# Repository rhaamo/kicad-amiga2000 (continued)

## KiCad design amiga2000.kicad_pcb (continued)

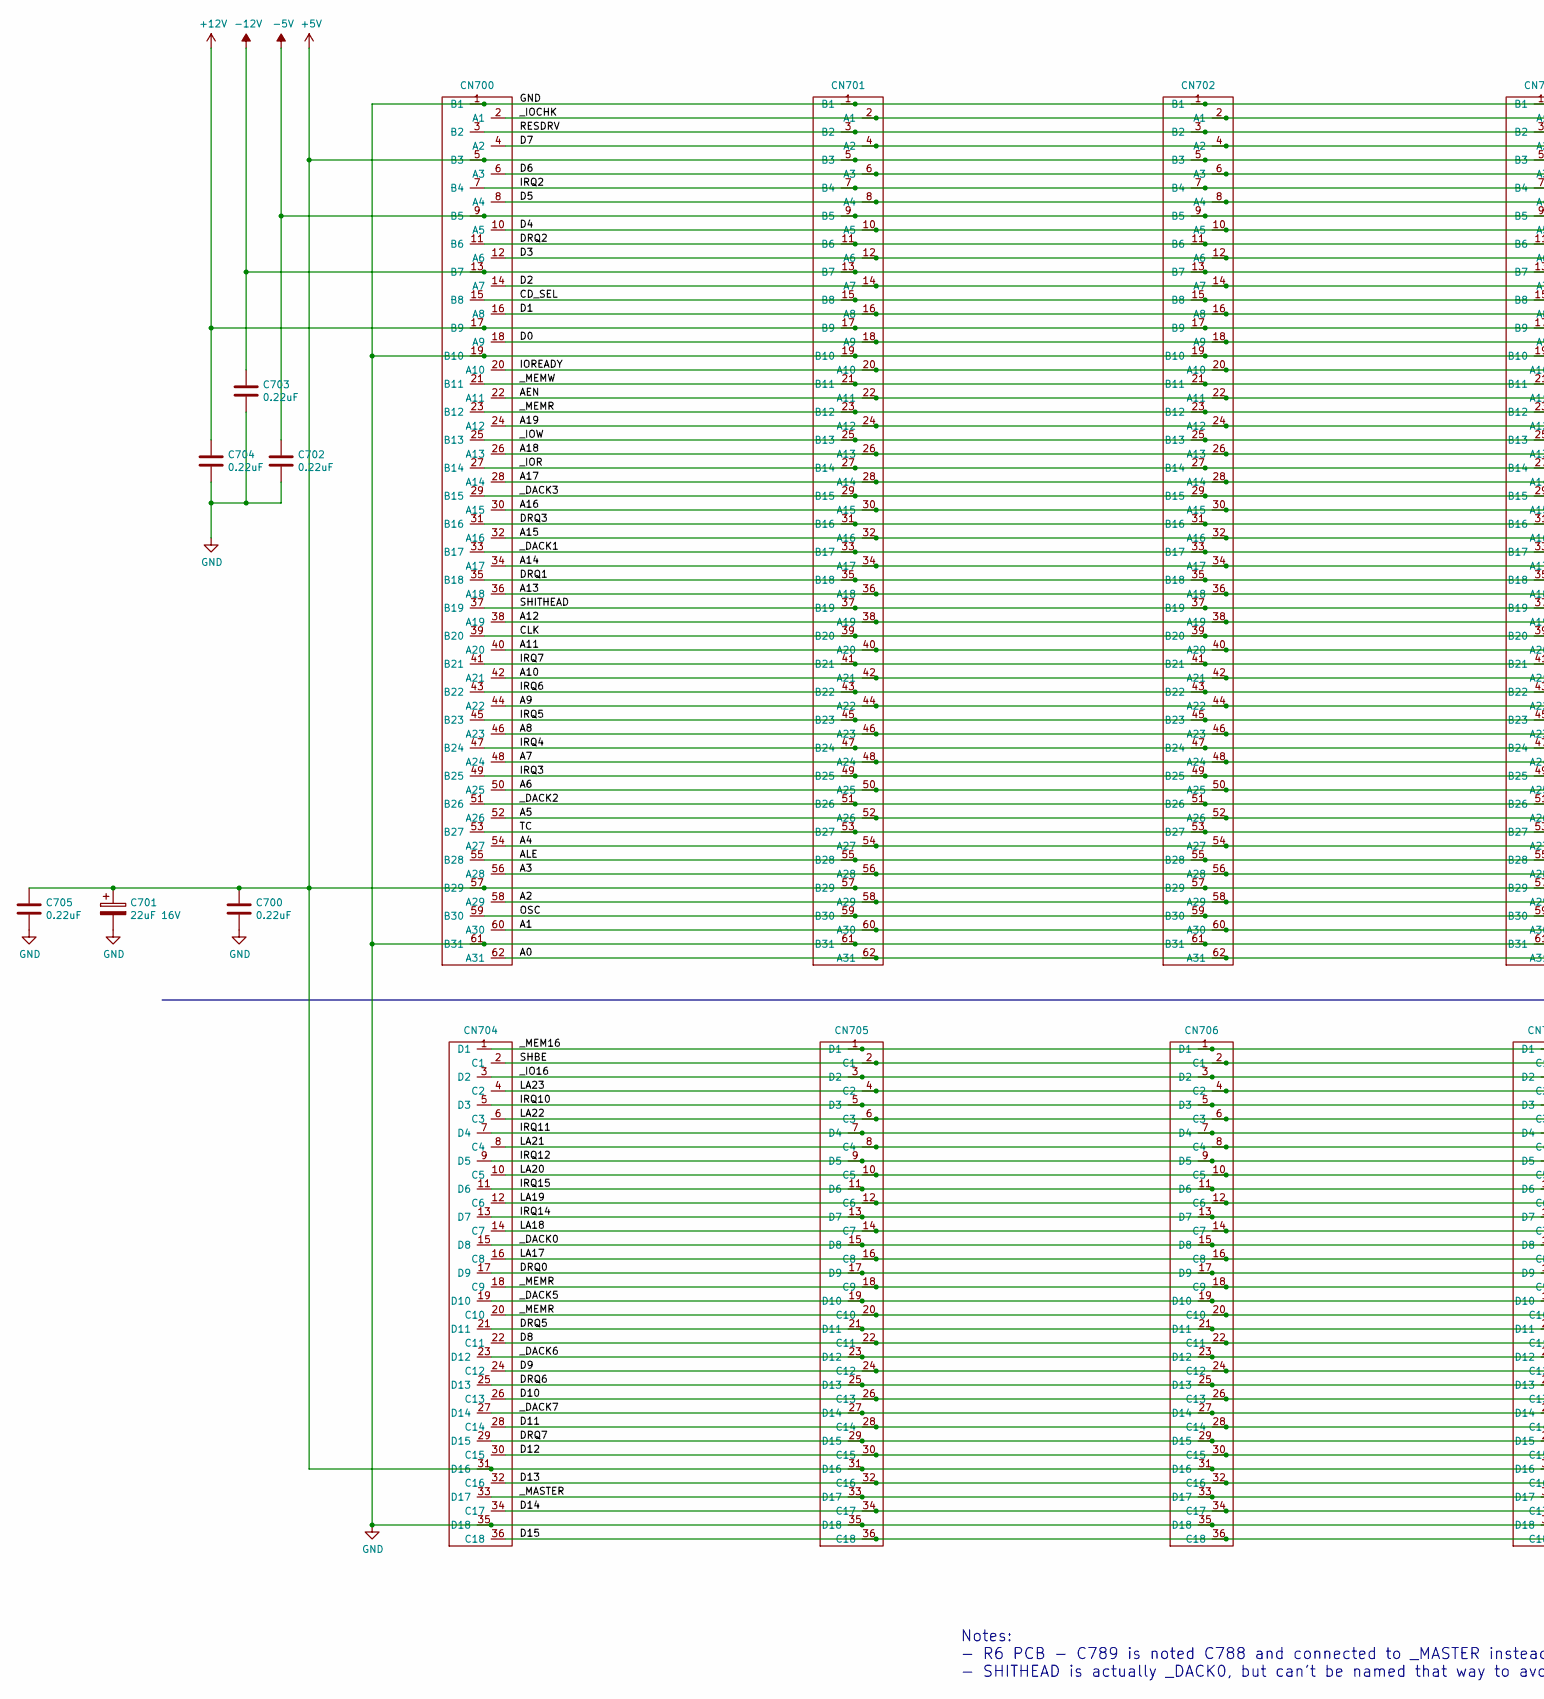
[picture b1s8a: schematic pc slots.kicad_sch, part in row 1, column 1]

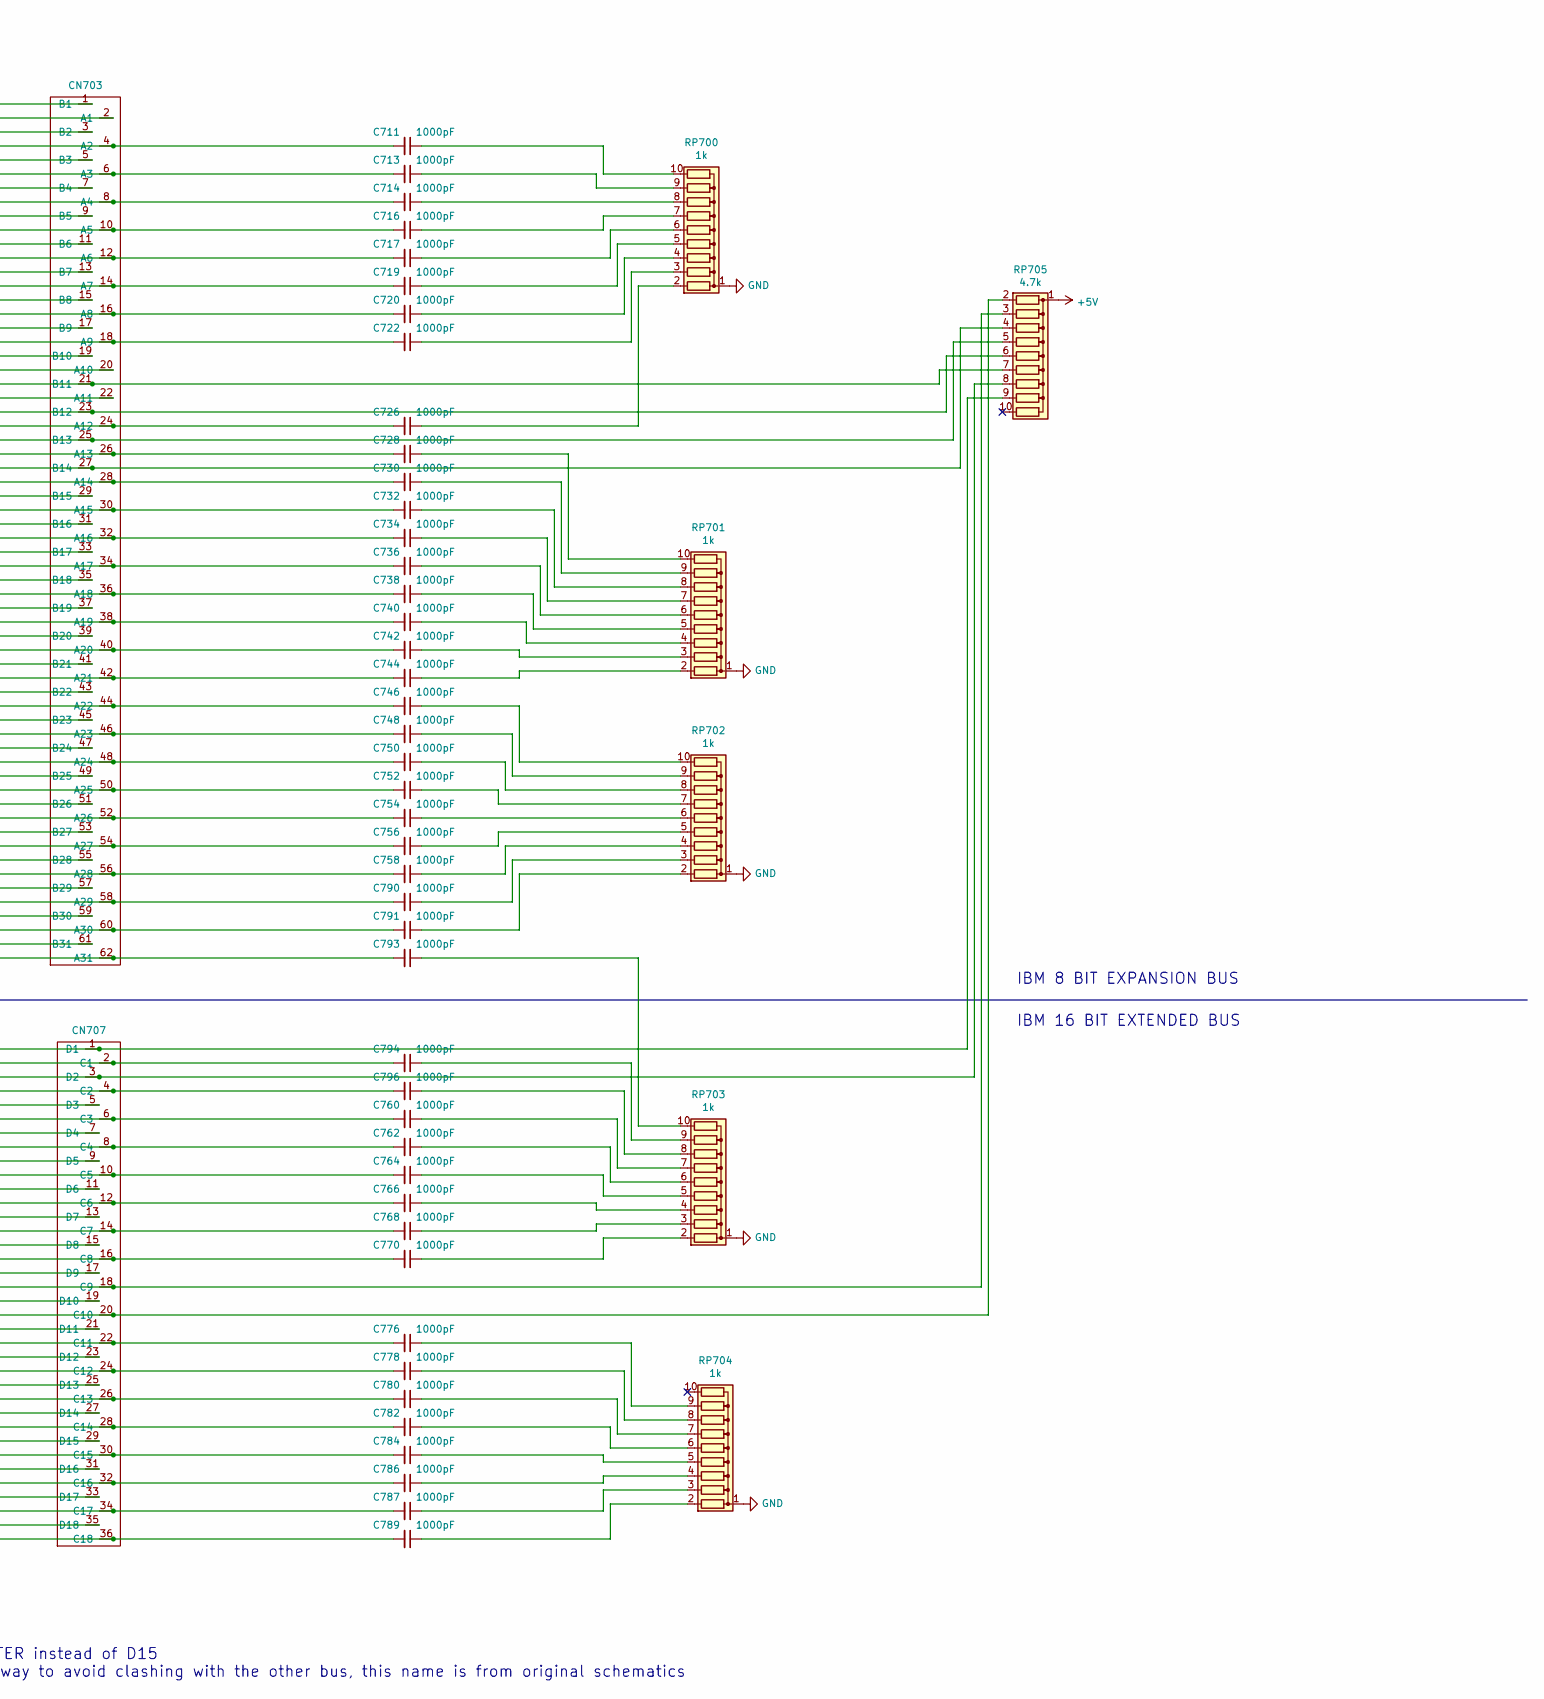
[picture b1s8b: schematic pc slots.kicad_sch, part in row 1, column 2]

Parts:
C700, C702, C703, C704, C705: 0.22uF; C_Rect_L11.5mm_W2.6mm_P10.00mm_MKT
C701: 22uF 16V; CP_Radial_Tantal_D5.0mm_P5.00mm
C711, C713, C714, C716, C717, C719, C720, C722, C726, C728, C730, C732, C734, C736, C738, C740, C742, C744, C746, C748, C750, C752, C754, C756, C758, C760, C762, C764, C766, C768, C770, C776, C778, C780, C782, C784, C786, C787, C789, C790, C791, C793, C794, C796: 1000pF; C_Rect_L11.5mm_W2.0mm_P10.00mm_MKT
CN700, CN701, CN702, CN703: IBM_8_BIT_EXPANSION_BUS; ISA8
CN704, CN705, CN706, CN707: IBM_16_BIT_EXTENDED_BUS; ISA16
RP700, RP701, RP702, RP703, RP704: 1k; R_Array_SIP10
RP705: 4.7k; R_Array_SIP10

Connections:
+12V: C704.1, CN700.17 (B9), CN701.17 (B9), CN702.17 (B9), CN703.17 (B9); also elsewhere on the board
-5V: C702.1, CN700.9 (B5), CN701.9 (B5), CN702.9 (B5), CN703.9 (B5); also elsewhere on the board
-12V: C703.1, CN700.13 (B7), CN701.13 (B7), CN702.13 (B7), CN703.13 (B7); also elsewhere on the board
/pc slots/A0: C793.2, CN700.62 (A31), CN701.62 (A31), CN702.62 (A31), CN703.62 (A31)
/pc slots/A1: C791.2, CN700.60 (A30), CN701.60 (A30), CN702.60 (A30), CN703.60 (A30)
/pc slots/A2: C790.2, CN700.58 (A29), CN701.58 (A29), CN702.58 (A29), CN703.58 (A29)
/pc slots/A3: C758.2, CN700.56 (A28), CN701.56 (A28), CN702.56 (A28), CN703.56 (A28)
/pc slots/A4: C756.2, CN700.54 (A27), CN701.54 (A27), CN702.54 (A27), CN703.54 (A27)
/pc slots/A5: C754.2, CN700.52 (A26), CN701.52 (A26), CN702.52 (A26), CN703.52 (A26)
/pc slots/A6: C752.2, CN700.50 (A25), CN701.50 (A25), CN702.50 (A25), CN703.50 (A25)
/pc slots/A7: C750.2, CN700.48 (A24), CN701.48 (A24), CN702.48 (A24), CN703.48 (A24)
/pc slots/A8: C748.2, CN700.46 (A23), CN701.46 (A23), CN702.46 (A23), CN703.46 (A23)
/pc slots/A9: C746.2, CN700.44 (A22), CN701.44 (A22), CN702.44 (A22), CN703.44 (A22)
/pc slots/A10: C744.2, CN700.42 (A21), CN701.42 (A21), CN702.42 (A21), CN703.42 (A21)
/pc slots/A11: C742.2, CN700.40 (A20), CN701.40 (A20), CN702.40 (A20), CN703.40 (A20)
/pc slots/A12: C740.2, CN700.38 (A19), CN701.38 (A19), CN702.38 (A19), CN703.38 (A19)
/pc slots/A13: C738.2, CN700.36 (A18), CN701.36 (A18), CN702.36 (A18), CN703.36 (A18)
/pc slots/A14: C736.2, CN700.34 (A17), CN701.34 (A17), CN702.34 (A17), CN703.34 (A17)
/pc slots/A15: C734.2, CN700.32 (A16), CN701.32 (A16), CN702.32 (A16), CN703.32 (A16)
/pc slots/A16: C732.2, CN700.30 (A15), CN701.30 (A15), CN702.30 (A15), CN703.30 (A15)
/pc slots/A17: C730.2, CN700.28 (A14), CN701.28 (A14), CN702.28 (A14), CN703.28 (A14)
/pc slots/A18: C728.2, CN700.26 (A13), CN701.26 (A13), CN702.26 (A13), CN703.26 (A13)
/pc slots/A19: C726.2, CN700.24 (A12), CN701.24 (A12), CN702.24 (A12), CN703.24 (A12)
/pc slots/AEN: CN700.22 (A11), CN701.22 (A11), CN702.22 (A11), CN703.22 (A11)
/pc slots/ALE: CN700.55 (B28), CN701.55 (B28), CN702.55 (B28), CN703.55 (B28)
/pc slots/CD_SEL: CN700.15 (B8), CN701.15 (B8), CN702.15 (B8), CN703.15 (B8)
/pc slots/CLK: CN700.39 (B20), CN701.39 (B20), CN702.39 (B20), CN703.39 (B20)
/pc slots/D0: C722.2, CN700.18 (A9), CN701.18 (A9), CN702.18 (A9), CN703.18 (A9)
/pc slots/D1: C720.2, CN700.16 (A8), CN701.16 (A8), CN702.16 (A8), CN703.16 (A8)
/pc slots/D2: C719.2, CN700.14 (A7), CN701.14 (A7), CN702.14 (A7), CN703.14 (A7)
/pc slots/D3: C717.2, CN700.12 (A6), CN701.12 (A6), CN702.12 (A6), CN703.12 (A6)
/pc slots/D4: C716.2, CN700.10 (A5), CN701.10 (A5), CN702.10 (A5), CN703.10 (A5)
/pc slots/D5: C714.2, CN700.8 (A4), CN701.8 (A4), CN702.8 (A4), CN703.8 (A4)
/pc slots/D6: C713.2, CN700.6 (A3), CN701.6 (A3), CN702.6 (A3), CN703.6 (A3)
/pc slots/D7: C711.2, CN700.4 (A2), CN701.4 (A2), CN702.4 (A2), CN703.4 (A2)
/pc slots/D8: C776.2, CN704.22 (C11), CN705.22 (C11), CN706.22 (C11), CN707.22 (C11)
/pc slots/D9: C778.2, CN704.24 (C12), CN705.24 (C12), CN706.24 (C12), CN707.24 (C12)
/pc slots/D10: C780.2, CN704.26 (C13), CN705.26 (C13), CN706.26 (C13), CN707.26 (C13)
/pc slots/D11: C782.2, CN704.28 (C14), CN705.28 (C14), CN706.28 (C14), CN707.28 (C14)
/pc slots/D12: C784.2, CN704.30 (C15), CN705.30 (C15), CN706.30 (C15), CN707.30 (C15)
/pc slots/D13: C786.2, CN704.32 (C16), CN705.32 (C16), CN706.32 (C16), CN707.32 (C16)
/pc slots/D14: C787.2, CN704.34 (C17), CN705.34 (C17), CN706.34 (C17), CN707.34 (C17)
/pc slots/D15: C789.2, CN704.36 (C18), CN705.36 (C18), CN706.36 (C18), CN707.36 (C18)
/pc slots/DRQ0: CN704.17 (D9), CN705.17 (D9), CN706.17 (D9), CN707.17 (D9)
/pc slots/DRQ1: CN700.35 (B18), CN701.35 (B18), CN702.35 (B18), CN703.35 (B18)
/pc slots/DRQ2: CN700.11 (B6), CN701.11 (B6), CN702.11 (B6), CN703.11 (B6)
/pc slots/DRQ3: CN700.31 (B16), CN701.31 (B16), CN702.31 (B16), CN703.31 (B16)
/pc slots/DRQ5: CN704.21 (D11), CN705.21 (D11), CN706.21 (D11), CN707.21 (D11)
/pc slots/DRQ6: CN704.25 (D13), CN705.25 (D13), CN706.25 (D13), CN707.25 (D13)
/pc slots/DRQ7: CN704.29 (D15), CN705.29 (D15), CN706.29 (D15), CN707.29 (D15)
/pc slots/IOREADY: CN700.20 (A10), CN701.20 (A10), CN702.20 (A10), CN703.20 (A10)
/pc slots/IRQ2: CN700.7 (B4), CN701.7 (B4), CN702.7 (B4), CN703.7 (B4)
/pc slots/IRQ3: CN700.49 (B25), CN701.49 (B25), CN702.49 (B25), CN703.49 (B25)
/pc slots/IRQ4: CN700.47 (B24), CN701.47 (B24), CN702.47 (B24), CN703.47 (B24)
/pc slots/IRQ5: CN700.45 (B23), CN701.45 (B23), CN702.45 (B23), CN703.45 (B23)
/pc slots/IRQ6: CN700.43 (B22), CN701.43 (B22), CN702.43 (B22), CN703.43 (B22)
/pc slots/IRQ7: CN700.41 (B21), CN701.41 (B21), CN702.41 (B21), CN703.41 (B21)
/pc slots/IRQ10: CN704.5 (D3), CN705.5 (D3), CN706.5 (D3), CN707.5 (D3)
/pc slots/IRQ11: CN704.7 (D4), CN705.7 (D4), CN706.7 (D4), CN707.7 (D4)
/pc slots/IRQ12: CN704.9 (D5), CN705.9 (D5), CN706.9 (D5), CN707.9 (D5)
/pc slots/IRQ14: CN704.13 (D7), CN705.13 (D7), CN706.13 (D7), CN707.13 (D7)
/pc slots/IRQ15: CN704.11 (D6), CN705.11 (D6), CN706.11 (D6), CN707.11 (D6)
/pc slots/LA17: C770.2, CN704.16 (C8), CN705.16 (C8), CN706.16 (C8), CN707.16 (C8)
/pc slots/LA18: C768.2, CN704.14 (C7), CN705.14 (C7), CN706.14 (C7), CN707.14 (C7)
/pc slots/LA19: C766.2, CN704.12 (C6), CN705.12 (C6), CN706.12 (C6), CN707.12 (C6)
/pc slots/LA20: C764.2, CN704.10 (C5), CN705.10 (C5), CN706.10 (C5), CN707.10 (C5)
/pc slots/LA21: C762.2, CN704.8 (C4), CN705.8 (C4), CN706.8 (C4), CN707.8 (C4)
/pc slots/LA22: C760.2, CN704.6 (C3), CN705.6 (C3), CN706.6 (C3), CN707.6 (C3)
/pc slots/LA23: C796.2, CN704.4 (C2), CN705.4 (C2), CN706.4 (C2), CN707.4 (C2)
/pc slots/OSC: CN700.59 (B30), CN701.59 (B30), CN702.59 (B30), CN703.59 (B30)
/pc slots/RESDRV: CN700.3 (B2), CN701.3 (B2), CN702.3 (B2), CN703.3 (B2)
/pc slots/SHBE: C794.2, CN704.2 (C1), CN705.2 (C1), CN706.2 (C1), CN707.2 (C1)
/pc slots/SHITHEAD: CN700.37 (B19), CN701.37 (B19), CN702.37 (B19), CN703.37 (B19)
/pc slots/TC: CN700.53 (B27), CN701.53 (B27), CN702.53 (B27), CN703.53 (B27)
/pc slots/_DACK0: CN704.15 (D8), CN705.15 (D8), CN706.15 (D8), CN707.15 (D8)
/pc slots/_DACK1: CN700.33 (B17), CN701.33 (B17), CN702.33 (B17), CN703.33 (B17)
/pc slots/_DACK2: CN700.51 (B26), CN701.51 (B26), CN702.51 (B26), CN703.51 (B26)
/pc slots/_DACK3: CN700.29 (B15), CN701.29 (B15), CN702.29 (B15), CN703.29 (B15)
/pc slots/_DACK5: CN704.19 (D10), CN705.19 (D10), CN706.19 (D10), CN707.19 (D10)
/pc slots/_DACK6: CN704.23 (D12), CN705.23 (D12), CN706.23 (D12), CN707.23 (D12)
/pc slots/_DACK7: CN704.27 (D14), CN705.27 (D14), CN706.27 (D14), CN707.27 (D14)
/pc slots/_IO16: CN704.3 (D2), CN705.3 (D2), CN706.3 (D2), CN707.3 (D2), RP705.8 (R7)
/pc slots/_IOCHK: CN700.2 (A1), CN701.2 (A1), CN702.2 (A1), CN703.2 (A1)
/pc slots/_IOR: CN700.27 (B14), CN701.27 (B14), CN702.27 (B14), CN703.27 (B14), RP705.4 (R3)
/pc slots/_IOW: CN700.25 (B13), CN701.25 (B13), CN702.25 (B13), CN703.25 (B13), RP705.5 (R4)
/pc slots/_MASTER: CN704.33 (D17), CN705.33 (D17), CN706.33 (D17), CN707.33 (D17)
/pc slots/_MEM16: CN704.1 (D1), CN705.1 (D1), CN706.1 (D1), CN707.1 (D1), RP705.9 (R8)
/pc slots/_MEMR: CN700.23 (B12), CN701.23 (B12), CN702.23 (B12), CN703.23 (B12), CN704.18 (C9), CN704.20 (C10), CN705.18 (C9), CN705.20 (C10), CN706.18 (C9), CN706.20 (C10), CN707.18 (C9), CN707.20 (C10), RP705.2 (R1), RP705.3 (R2), RP705.6 (R5)
/pc slots/_MEMW: CN700.21 (B11), CN701.21 (B11), CN702.21 (B11), CN703.21 (B11), RP705.7 (R6)
GND: C700.2, C701.2, C702.2, C703.2, C704.2, C705.2, CN700.1 (B1), CN700.19 (B10), CN700.61 (B31), CN701.1 (B1), CN701.19 (B10), CN701.61 (B31), CN702.1 (B1), CN702.19 (B10), CN702.61 (B31), CN703.1 (B1), CN703.19 (B10), CN703.61 (B31), CN704.35 (D18), CN705.35 (D18), CN706.35 (D18), CN707.35 (D18), RP700.1 (common), RP701.1 (common), RP702.1 (common), RP703.1 (common), RP704.1 (common); also elsewhere on the board
unnamed: C711.1, RP700.10 (R9)
unnamed: C713.1, RP700.9 (R8)
unnamed: C714.1, RP700.8 (R7)
unnamed: C716.1, RP700.7 (R6)
unnamed: C717.1, RP700.6 (R5)
unnamed: C719.1, RP700.5 (R4)
unnamed: C720.1, RP700.4 (R3)
unnamed: C722.1, RP700.3 (R2)
unnamed: C726.1, RP700.2 (R1)
unnamed: C728.1, RP701.10 (R9)
unnamed: C730.1, RP701.9 (R8)
unnamed: C732.1, RP701.8 (R7)
unnamed: C734.1, RP701.7 (R6)
unnamed: C736.1, RP701.6 (R5)
unnamed: C738.1, RP701.5 (R4)
unnamed: C740.1, RP701.4 (R3)
unnamed: C742.1, RP701.3 (R2)
unnamed: C744.1, RP701.2 (R1)
unnamed: C746.1, RP702.10 (R9)
unnamed: C748.1, RP702.9 (R8)
unnamed: C750.1, RP702.8 (R7)
unnamed: C752.1, RP702.7 (R6)
unnamed: C754.1, RP702.6 (R5)
unnamed: C756.1, RP702.5 (R4)
unnamed: C758.1, RP702.4 (R3)
unnamed: C760.1, RP703.7 (R6)
unnamed: C762.1, RP703.6 (R5)
unnamed: C764.1, RP703.5 (R4)
unnamed: C766.1, RP703.4 (R3)
unnamed: C768.1, RP703.3 (R2)
unnamed: C770.1, RP703.2 (R1)
unnamed: C776.1, RP704.9 (R8)
unnamed: C778.1, RP704.8 (R7)
unnamed: C780.1, RP704.7 (R6)
unnamed: C782.1, RP704.6 (R5)
unnamed: C784.1, RP704.5 (R4)
unnamed: C786.1, RP704.4 (R3)
unnamed: C787.1, RP704.3 (R2)
unnamed: C789.1, RP704.2 (R1)
unnamed: C790.1, RP702.3 (R2)
unnamed: C791.1, RP702.2 (R1)
unnamed: C793.1, RP703.10 (R9)
unnamed: C794.1, RP703.9 (R8)
unnamed: C796.1, RP703.8 (R7)

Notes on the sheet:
IBM 8 BIT EXPANSION BUS
IBM 16 BIT EXTENDED BUS
Notes: - R6 PCB - C789 is noted C788 and connected to _MASTER instead of D15 - SHITHEAD is actually _DACK0, but can't be named that way to avoid clashing with the other bus, this name is from original schematics

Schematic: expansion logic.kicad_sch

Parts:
BT800: 3/60DK Ni-Cd 3.6V 60mAH; PinSocket_2x01_P2.54mm_Vertical
C800, C802, C803, C804, C812: 0.1uF; C_Rect_L11.5mm_W2.6mm_P10.00mm_MKT
C810: 20pF; C_Rect_L11.5mm_W2.6mm_P10.00mm_MKT
C811: 4.7uF 16V; CP_Radial_D5.0mm_P2.50mm
C904, C920: 100pF; C_Rect_L11.5mm_W2.6mm_P10.00mm_MKT
D800, D801: 1N4148; D_DO-35_SOD27_P7.62mm_Horizontal
R2, R800: 1k; R_Axial_DIN0207_L6.3mm_D2.5mm_P10.16mm_Horizontal
R801, R803: 470; R_Axial_DIN0207_L6.3mm_D2.5mm_P10.16mm_Horizontal
R804: 10k; R_Axial_DIN0207_L6.3mm_D2.5mm_P10.16mm_Horizontal
R806, R807: 4.7k; R_Axial_DIN0207_L6.3mm_D2.5mm_P10.16mm_Horizontal
R904, R905: 47; R_Axial_DIN0207_L6.3mm_D2.5mm_P10.16mm_Horizontal
RP800: 1k; R_Array_SIP8
RP801: 4.7k; R_Array_SIP8
U302: 74LS32; DIP-14_W7.62mm_Socket
U800: BUSTER5721; DIP-48_W15.24mm_Socket
U801: MSM6242; DIP-18_W7.62mm_Socket
U802: 74LS138; DIP-16_W7.62mm_Socket
U803: 74LS08; DIP-14_W7.62mm_Socket
U804: 74LS148; DIP-16_W7.62mm_Socket
VC800: 22-47pF; C_Rect_L7.0mm_W6.5mm_P5.00mm
Y800: 32768Hz; Crystal_DS15_D1.5mm_L5.0mm_Horizontal

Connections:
+12V: R801.1; also elsewhere on the board
A2: U801.4 (A0); also elsewhere on the board
A3: U801.5 (A1); also elsewhere on the board
A4: U801.6 (A2); also elsewhere on the board
A5: U801.7 (A3); also elsewhere on the board
BA19: U800.30 (_A19); also elsewhere on the board
BA20: U800.31 (_A20); also elsewhere on the board
BA21: U800.32 (_A21); also elsewhere on the board
BA22: U800.33 (_A22); also elsewhere on the board
BA23: U800.34 (_A23); also elsewhere on the board
C1: U800.19 (C1); also elsewhere on the board
C3: U800.20 (C3); also elsewhere on the board
D0: U801.14 (D0); also elsewhere on the board
D1: U801.13 (D1); also elsewhere on the board
D2: U801.12 (D2); also elsewhere on the board
D3: U801.11 (D3); also elsewhere on the board
DMAOUT: U302.11; also elsewhere on the board
DOE: R904.1; also elsewhere on the board
GND: BT800.2 (-), C800.1, C802.1, C803.2, C804.2, C810.2, C811.2, C812.2, C904.2, C920.2, U302.13, U800.1 (GND), U800.24 (GND), U800.43 (TEST), U801.2 (_CS0), U801.9 (GND), U802.4 (E1), U802.5 (E2), U802.8 (GND), U803.7 (GND), U804.5 (EI), U804.8 (GND), VC800.2; also elsewhere on the board
unnamed: BT800.1 (+), R803.2
unnamed: C810.1, U801.17 (_XT), Y800.1
unnamed: C811.1, C812.1, D801.1 (K), R803.1, U801.18 (VCC)
unnamed: D800.2 (A), D801.2 (A), R801.2
unnamed: R804.2, U801.1 (STDP)
unnamed: R904.2, U800.47 (DOE)
unnamed: R905.1, U800.22 (_C4)
unnamed: U801.16 (XT), VC800.1, Y800.2
unnamed: U802.9 (O6), U803.1
unnamed: U802.10 (O5), U804.12 (I2)
unnamed: U802.11 (O4), U804.13 (I3)
unnamed: U802.12 (O3), U803.4
unnamed: U802.13 (O2), U803.9
unnamed: U802.14 (O1), U804.3 (I6)
unnamed: U802.15 (O0), U803.12
unnamed: U803.3, U804.11 (I1)
unnamed: U803.6, U804.1 (I4)
unnamed: U803.8, U804.2 (I5)
unnamed: U803.11, U804.4 (I7)
READ: U800.35 (READ); also elsewhere on the board
_BAS: R2.2, U800.36 (_AS); also elsewhere on the board
_BEER: U800.26 (_BEER); also elsewhere on the board
_BG: U800.17 (_BG); also elsewhere on the board
_BG1: U800.2 (_BG1); also elsewhere on the board
_BG2: U800.3 (_BG2); also elsewhere on the board
_BG3: U800.4 (_BG3); also elsewhere on the board
_BG4: U800.5 (_BG4); also elsewhere on the board
_BG5: U800.6 (_BG5); also elsewhere on the board
_BLDS: U800.37 (_LDS); also elsewhere on the board
_BOSS: U800.39 (_BOSS); also elsewhere on the board
_BR: U800.27 (_BR); also elsewhere on the board
_BR1: U800.7 (_BR1); also elsewhere on the board
_BR2: U800.8 (_BR2); also elsewhere on the board
_BR3: U800.9 (_BR3); also elsewhere on the board
_BR4: U800.10 (_BR4); also elsewhere on the board
_BR5: U800.11 (_BR5); also elsewhere on the board
_BRST: U800.42 (_RST); also elsewhere on the board
_BUDS: U800.38 (_UDS); also elsewhere on the board
_C2: C904.1, U800.21 (_C2); also elsewhere on the board
_C4: C920.1, R905.2; also elsewhere on the board
_CBG: R806.1, U800.29 (_CBG); also elsewhere on the board
_CBR: R807.1, U800.28 (_CBR); also elsewhere on the board
_CDAC: U800.18 (_CDAC); also elsewhere on the board
_CIPL0: RP801.4 (R3), U802.1 (A0); also elsewhere on the board
_CIPL1: RP801.3 (R2), U802.2 (A1); also elsewhere on the board
_CIPL2: RP801.2 (R1), U802.3 (A2); also elsewhere on the board
_CLKRD: U801.8 (_RD); also elsewhere on the board
_CLKWR: U801.10 (_WR); also elsewhere on the board
_D2P: U800.45 (_D2P); also elsewhere on the board
_DBOE: U800.46 (_DBOE); also elsewhere on the board
_EINT1: RP801.8 (R7), U803.2; also elsewhere on the board
_EINT4: RP801.7 (R6), U803.5; also elsewhere on the board
_EINT5: RP801.6 (R5), U803.10; also elsewhere on the board
_EINT7: RP801.5 (R4), U803.13; also elsewhere on the board
_GBG: U800.23 (_GBG); also elsewhere on the board
_IPL0: U804.9 (S0); also elsewhere on the board
_IPL1: U804.7 (S1); also elsewhere on the board
_IPL2: U804.6 (S2); also elsewhere on the board
_OVR: U800.40 (_OVR); also elsewhere on the board
_OWN: R800.1, U302.12, U800.41 (_OWN); also elsewhere on the board
_SLAVE1: RP800.6 (R5), U800.12 (_SLAVE1); also elsewhere on the board
_SLAVE2: RP800.5 (R4), U800.13 (_SLAVE2); also elsewhere on the board
_SLAVE3: RP800.4 (R3), U800.14 (_SLAVE3); also elsewhere on the board
_SLAVE4: RP800.3 (R2), U800.15 (_SLAVE4); also elsewhere on the board
_SLAVE5: RP800.2 (R1), U800.16 (_SLAVE5); also elsewhere on the board

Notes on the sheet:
REV 6.2 fix p36 to +5 via 1k

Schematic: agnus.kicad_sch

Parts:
C101, C102, C107, C108, C110, C918: 0.1uF; C_Rect_L11.5mm_W2.6mm_P10.00mm_MKT
C415: 4.7uF 16V; CP_Radial_D5.0mm_P2.50mm
C905, C907, C908: 100pF; C_Rect_L11.5mm_W2.6mm_P10.00mm_MKT
FB101, FB907: Ferrite_Bead_Small; L_Axial_L7.0mm_D3.3mm_P10.16mm_Horizontal_Fastron_MICC
FB102: Ferrite_Bead_Small; L_Axial_L9.5mm_D4.0mm_P15.24mm_Horizontal_Fastron_SMCC
J101: Conn_01x03_Male; PinHeader_1x03_P2.54mm_Vertical
J102: Jumper_2_Open; SolderJumper-2_P1.3mm_Open_RoundedPad1.0x1.5mm
J900: Jumper_2_Bridged; PinHeader_2x01_P2.54mm_Vertical
R101, R109, R916: 4.7k; R_Axial_DIN0207_L6.3mm_D2.5mm_P10.16mm_Horizontal
R105, R106: 22; R_Axial_DIN0207_L6.3mm_D2.5mm_P10.16mm_Horizontal
R110, R114, R115: 330; R_Axial_DIN0207_L6.3mm_D2.5mm_P10.16mm_Horizontal
RP102, RP902, RP907: 47 (isolated, pack); R_Array_SIP8
U101: AGNUS8372; PLCC-84_THT-Socket
U102: GARY5719; DIP-48_W15.24mm_Socket
U107: 74F04; DIP-14_W7.62mm_Socket
U108: 74LS74A; DIP-14_W7.62mm_Socket
U302: 74LS32; DIP-14_W7.62mm_Socket
U900: 74F00; DIP-14_W7.62mm_Socket
X1: 28.37516MHz (pal); Oscillator_DIP-14

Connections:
7M: RP907.6 (R3.2); also elsewhere on the board
28M: FB101.1, U101.34 (28MHZ); also elsewhere on the board
A1: U101.60 (A1); also elsewhere on the board
A2: U101.61 (A2); also elsewhere on the board
A3: U101.62 (A3); also elsewhere on the board
A4: U101.63 (A4); also elsewhere on the board
A5: U101.64 (A5); also elsewhere on the board
A6: U101.65 (A6); also elsewhere on the board
A7: U101.66 (A7); also elsewhere on the board
A8: U101.67 (A8); also elsewhere on the board
A9: U101.68 (A9); also elsewhere on the board
A10: U101.69 (A10); also elsewhere on the board
A11: U101.70 (A11); also elsewhere on the board
A12: U101.71 (A12); also elsewhere on the board
A13: U101.72 (A13); also elsewhere on the board
A14: U101.73 (A14); also elsewhere on the board
A15: U101.74 (A15); also elsewhere on the board
A16: U101.75 (A16); also elsewhere on the board
A17: U101.76 (A17), U102.33 (A17); also elsewhere on the board
A18: U101.77 (A18), U102.34 (A18); also elsewhere on the board
A19: J101.3, U102.35 (A19); also elsewhere on the board
A20: U102.36 (A20); also elsewhere on the board
A21: U102.37 (A21); also elsewhere on the board
A22: U102.38 (A22); also elsewhere on the board
A23: J101.1, U102.39 (A23); also elsewhere on the board
C1: C907.1, U101.40 (CCK), U102.28 (CCK), U107.3, U107.13; also elsewhere on the board
C3: C908.1, U101.39 (CCKQ), U102.27 (CCKQ), U107.5, U107.9; also elsewhere on the board
DMAL: U101.18 (DMAL); also elsewhere on the board
DRA0: U101.43 (DRA0); also elsewhere on the board
DRA1: U101.44 (DRA1); also elsewhere on the board
DRA2: U101.45 (DRA2); also elsewhere on the board
DRA3: U101.46 (DRA3); also elsewhere on the board
DRA4: U101.47 (DRA4); also elsewhere on the board
DRA5: U101.48 (DRA5); also elsewhere on the board
DRA6: U101.49 (DRA6); also elsewhere on the board
DRA7: U101.50 (DRA7); also elsewhere on the board
DRA8: U101.51 (DRA8); also elsewhere on the board
DRD0: U101.14 (DRD0); also elsewhere on the board
DRD1: U101.13 (DRD1); also elsewhere on the board
DRD2: U101.12 (DRD2); also elsewhere on the board
DRD3: U101.11 (DRD3); also elsewhere on the board
DRD4: U101.10 (DRD4); also elsewhere on the board
DRD5: U101.9 (DRD5); also elsewhere on the board
DRD6: U101.8 (DRD6); also elsewhere on the board
DRD7: U101.7 (DRD7); also elsewhere on the board
DRD8: U101.6 (DRD8); also elsewhere on the board
DRD9: U101.5 (DRD9); also elsewhere on the board
DRD10: U101.4 (DRD10); also elsewhere on the board
DRD11: U101.3 (DRD11); also elsewhere on the board
DRD12: U101.2 (DRD12); also elsewhere on the board
DRD13: U101.1 (DRD13); also elsewhere on the board
DRD14: U101.84 (DRD14); also elsewhere on the board
DRD15: U101.83 (DRD15); also elsewhere on the board
E7M: RP907.1 (R1.1); also elsewhere on the board
ECDAC: RP902.8 (R4.2); also elsewhere on the board
GND: C101.2, C102.2, C107.2, C108.2, C110.2, C415.2, C905.1, C907.2, C908.2, C918.2, J102.2 (B), R110.2, U101.42 (VSS1), U101.58 (VSS2), U101.82 (VSS3), U102.1 (GND), U102.24 (GND), U102.40 (NC), U107.7 (GND), U108.7 (GND), U302.10, U900.7 (GND), X1.7 (GND); also elsewhere on the board
unnamed: C905.2, FB102.1, U102.25 (_LATCH)
unnamed: FB101.2, X1.8 (OUT)
unnamed: FB907.2, RP102.1 (R1.1)
unnamed: J101.2, U101.59 (A19)
unnamed: J102.1 (A), R101.1, U101.41 (PAL/_NTSC)
unnamed: J900.2 (B), R916.1, U102.14 (_BGACK)
unnamed: R105.1, U102.2 (_VPA)
unnamed: R106.1, U102.43 (_DTACK)
unnamed: RP102.2 (R1.2), U107.8
unnamed: RP102.3 (R2.1), U107.6
unnamed: RP102.6 (R3.2), RP102.7 (R4.1), U107.4
unnamed: RP902.3 (R2.1), U107.12
unnamed: RP902.6 (R3.2), U107.10
unnamed: RP902.7 (R4.1), U107.2
unnamed: RP907.2 (R1.2), U302.8
unnamed: RP907.3 (R2.1), RP907.5 (R3.1), U101.38 (7MHz), U302.9
unnamed: U101.19 (_BLISS), U102.19 (_BLISS)
unnamed: U101.20 (_BLIT), U900.12
unnamed: U101.23 (_REGEN), U102.18 (_REGEN)
unnamed: U101.25 (_RAMEN), U102.20 (_RAMEN)
unnamed: U102.15 (_BLIT), U900.8
unnamed: U900.10, U900.11
OVL: U102.30 (OVL); also elsewhere on the board
RGA1: U101.33 (RGA1); also elsewhere on the board
RGA2: U101.32 (RGA2); also elsewhere on the board
RGA3: U101.31 (RGA3); also elsewhere on the board
RGA4: U101.30 (RGA4); also elsewhere on the board
RGA5: U101.29 (RGA5); also elsewhere on the board
RGA6: U101.28 (RGA6); also elsewhere on the board
RGA7: U101.27 (RGA7); also elsewhere on the board
RGA8: U101.26 (RGA8); also elsewhere on the board
R_W: U101.22 (R/W), U102.12 (R/W); also elsewhere on the board
V7M: RP907.4 (R2.2); also elsewhere on the board
VCDAC: RP902.5 (R3.1); also elsewhere on the board
XCLK: R110.1, U101.35 (XCLK); also elsewhere on the board
XRDY: R114.2, U102.31 (XRDY); also elsewhere on the board
_AS: U101.24 (_AS), U102.13 (_AS); also elsewhere on the board
_BGACK: J900.1 (A); also elsewhere on the board
_CASL: U101.54 (_CASL); also elsewhere on the board
_CASU: U101.55 (_CASU); also elsewhere on the board
_CDAC: U101.37 (_CDAC), U102.26 (_CDAC), U107.1, U107.11; also elsewhere on the board
_CLKRD: U102.22 (_CLKRD); also elsewhere on the board
_CLKWR: U102.23 (_CLKWR); also elsewhere on the board
_CSYNC: U101.80 (_CSYNC); also elsewhere on the board
_DTACK: R106.2; also elsewhere on the board
_EC1: RP902.4 (R2.2); also elsewhere on the board
_EC3: FB907.1; also elsewhere on the board
_EXRAM: U102.32 (_EXRAM); also elsewhere on the board
_HLT: U102.42 (_HLT); also elsewhere on the board
_HSYNC: U101.81 (_HSYNC); also elsewhere on the board
_INT3: U101.17 (_INTR); also elsewhere on the board
_LATCH: FB102.2; also elsewhere on the board
_LDS: U101.52 (_LDS), U102.10 (_LDS); also elsewhere on the board
_LPEN: U101.78 (_LPEN); also elsewhere on the board
_MC1: RP102.8 (R4.2); also elsewhere on the board
_OEB: U102.4 (_OEB); also elsewhere on the board
_OEL: U102.3 (_OEL); also elsewhere on the board
_OVR: R115.2, U102.29 (_OVR); also elsewhere on the board
_RAS0: U101.57 (_RAS0); also elsewhere on the board
_RAS1: U101.56 (_RAS1); also elsewhere on the board
_ROMEN: U102.21 (_ROMEN), U900.9; also elsewhere on the board
_RST: U101.16 (_RESET), U102.41 (_RST); also elsewhere on the board
_UDS: U101.53 (_UDS), U102.11 (_UDS); also elsewhere on the board
_VC1: RP102.5 (R3.1); also elsewhere on the board
_VC3: RP102.4 (R2.2); also elsewhere on the board
_VPA: R105.2; also elsewhere on the board
_VSYNC: U101.79 (_VSYNC); also elsewhere on the board
_WE: U101.21 (_WE); also elsewhere on the board
_XCLKEN: R109.1, U101.36 (_XCLKEN); also elsewhere on the board

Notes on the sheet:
J102 open : PAL closed : NTSC
normal special

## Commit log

2019-05-26 sources
2019-05-26 Placeholders; Processor done
2019-05-28 Use correct source rev6. mostly all schematics done for first pass...
2019-05-28 Remove Vref as it's a local label of the sheet
2019-05-28 Some fixes
2019-05-28 Add tools
2019-05-29 All done; now to review
2019-05-29 Rev is 6.0
2019-05-29 readme
2019-05-29 urgh
2019-05-29 Fix some DRC fuckery
2019-05-29 Rename bus with correct syntax
2019-05-29 Some ERC things
2019-05-29 Rename some bus things
2019-05-29 Fix a bunch of DRC errors
2019-05-29 squeak
2019-05-29 More final ERC fixes
2019-05-29 Include BOMs
2019-05-29 mhhh
2019-05-29 Implemented various rev 6.2 fixes from forums and my own board
2019-05-29 Bump rev, update readme
2019-05-31 Rev 6.2 fixes are now documented properly
2019-05-31 REV 6.2 fixes applied
2019-05-31 Fix missing bus address
2019-05-31 Misread the PCB; It's effectively E and not A1
2019-05-31 Add PDF of schematics
2019-06-01 Fix the fixes
2019-06-01 This is now useless
2019-06-01 Document rev 6.3 and 6.4 fixes here
2019-06-03 hmmmm
2019-06-03 Review started; oopsie whoopsie
2019-06-03 Add gender to connectors
2019-06-03 Re ran annotate; bom; plot
2019-06-03 Review update
2019-06-04 One more review
2019-06-04 Power review; Add missing mouting holes
2019-06-04 Spotted error in original scanned schematics
2019-06-05 whoopsie
2019-06-05 Will make next kicad DRC happy
2019-06-05 more done
2019-06-12 Add submodule
2019-06-12 Use submodules for libs
2019-06-12 Review done
2019-06-12 kbd ok
2019-06-12 All reviews done
2019-06-13 Associate footprints with components
2019-06-13 Regenerate netlist
2019-06-15 Associate more components
2019-06-15 Change namings
2019-06-15 Update libs
2019-06-15 Associate ISA slots
2019-06-15 Update footprints
2019-06-15 Components associations finished; regenered netlist and pdf
2019-06-15 Fix numbering
2019-06-15 grrr
2019-06-15 fix fuckup
2019-06-15 Continue placing things
2019-06-15 More placement
2019-06-16 first placement pass is done
2019-06-16 mod: breakout INT2/OVR to pin header
2019-06-16 Remove old layer used for layouting
2019-06-16 Define track widths
2019-06-16 Make caps footprint smaller
2019-06-16 All components have been realigned; plus small sizes changes
2019-06-16 Makes the DRC happy
2019-06-16 It's ok
2019-06-16 Add explanation for jumpers
2019-06-16 better
2019-06-16 Replot and regenerate BOM
2019-06-16 Add interactive bom
2019-06-16 Din keyboard update
2019-06-16 warning
2019-06-16 Now with F DB23, connectors are ok
2019-06-16 Regenerate both BOMs after using the right DB23 M/F
2019-06-17 Correct some components orientation
2019-06-17 Fix capacitor error; regen files
2019-06-17 Add DoNotPopulate field for components which shouldn't be fitted
2019-06-17 Correct some datasheets
2019-06-17 Switch footprints for suitable modern replacements
2019-06-17 Some footprints updates; Add all Mouser references
2019-06-19 Got the components, reduce some footprints
2019-06-19 Some footprint changes; Tidy pcb
2019-06-19 Board have been autorouted
2019-06-19 Add gerbers
2019-06-28 Update README with various notes
2019-06-28 again
2019-07-22 Add pictures
2019-07-22 Reduce file size
2019-08-04 Set the various PN as a table
2019-08-04 pins
2019-08-04 oops
2019-08-06 Add power connector ref
2019-08-14 Fix CSV
2019-08-14 Add orig broken csv
2021-05-02 Fix joystick ports; Regenerate gerbers and schematics
2021-05-02 Update gerbers archive
2023-04-24 remove legacy files
2023-04-24 Add kicad7 files; add note for ISA bus signal name
